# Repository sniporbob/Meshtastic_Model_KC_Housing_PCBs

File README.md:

# Meshtastic_Model_KC_Housing_PCBs
PCB files for the Model KC meshtastic housing. There is an internal board that uses 2 target discs and gets epoxied into the base of the housing, and there's a charger board that holds a pair of pogo pins and allows soldering wires from a USB cable.

0.118" x 0.065" Target discs: part number 1618-4-57-15-00-00-03-0 from Mill-Max

Pogo Pins: P75-E2 from Amazon - https://www.amazon.com/dp/B099F1DRYJ - 16.54mm total length, 2.54mm compression, 1.02mm shaft diameter

Files in this repository include KiCad 8 project files and pre-generated gerber files. I milled these boards myself on a 3018 CNC mill so there are also panel layout KiCad files which are probably not useful to anyone.

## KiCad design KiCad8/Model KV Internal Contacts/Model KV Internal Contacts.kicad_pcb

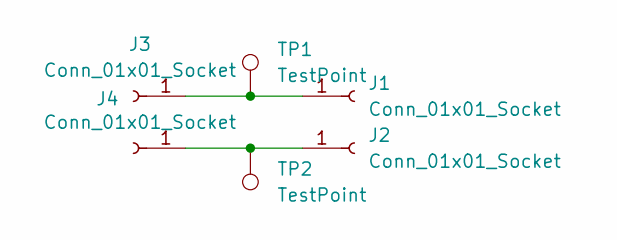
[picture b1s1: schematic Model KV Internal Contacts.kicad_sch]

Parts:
J1, J2: Conn_01x01_Socket; TestPoint_Pad_D3.0mm
J3, J4: Conn_01x01_Socket; PinHeader_1x01_P2.54mm_Vertical
TP1, TP2: TestPoint; TestPoint_Pad_1.5x1.5mm

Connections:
unnamed: J1.1, J3.1, TP1.1
unnamed: J2.1, J4.1, TP2.1

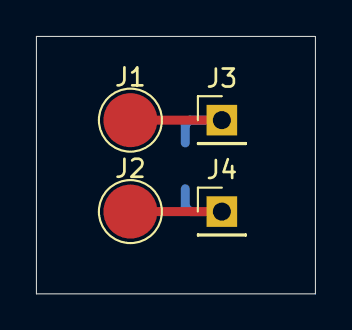
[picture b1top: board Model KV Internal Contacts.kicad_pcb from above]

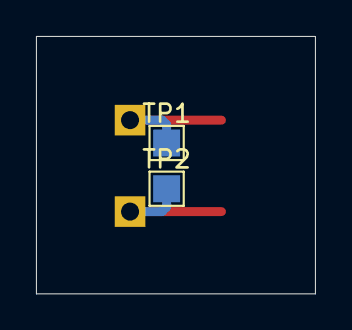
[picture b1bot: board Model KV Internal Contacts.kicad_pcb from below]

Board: 2 copper layers, 15.5 x 14.3 mm, 6 parts (2 on the bottom side), 2 nets.

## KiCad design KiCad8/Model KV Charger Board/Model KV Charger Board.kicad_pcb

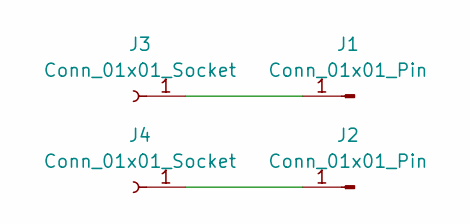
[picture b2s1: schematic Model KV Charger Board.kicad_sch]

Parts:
J1, J2: Conn_01x01_Pin; TestPoint_THTPad_D2.0mm_Drill1.0mm
J3, J4: Conn_01x01_Socket; TestPoint_THTPad_D2.5mm_Drill1.2mm

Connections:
unnamed: J1.1, J3.1
unnamed: J2.1, J4.1

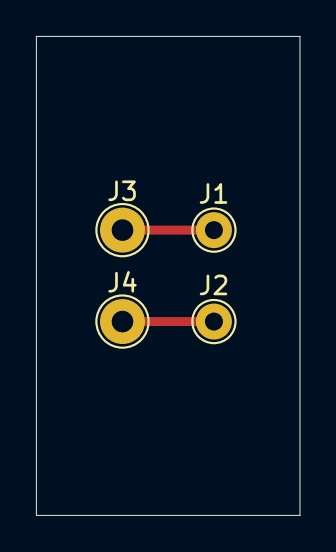
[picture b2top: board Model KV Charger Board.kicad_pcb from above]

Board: 2 copper layers, 14.6 x 26.6 mm, 4 parts (0 on the bottom side), 2 nets.

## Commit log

2026-05-04 Enhance README with board and component details
    Expanded the README with details about the internal board and components used, including target discs and pogo pins.
2026-05-04 Missing newline
    Missing newline
